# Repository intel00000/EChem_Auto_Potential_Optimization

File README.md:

<!-- @format -->

# Electrochemistry Reactor Controller User Interface

This repository contains a Electrochemistry Reactor Controller User Interface implemented in Python, utilizing multiple microcontrollers for hardware control and a PC-side GUI for experimental automation and operations.

See the [Release Page](https://github.com/intel00000/EChem_Auto_Potential_Optimization/releases) for:

<ol>
  <li>the latest pre-built executable for Windows</li>
  <li>the .uf2 firmwares for microcontroller</li>
  <li>the data post-processing scripts</li>
</ol>

Screenshots of the GUI are shown below. The GUI is designed to be user-friendly, allowing users to easily set up and control the pumps, valves, and other components of the electrochemistry reactor.

## Table of Contents

- [Requirements](#requirements)
- [Setup](#setup)
  - [Native Installation](#native-installation)
  - [Using a Python Virtual Environment (Recommended)](#using-a-python-virtual-environment-recommended)
- [Running the Application](#running-the-application)
- [Compiling to an Executable](#compiling-to-an-executable)
- [Usage](#usage)
- [File Descriptions](#file-descriptions)

## Requirements

- Python 3.11 or higher
- Pip package manager

## Setup (two methods)

### 1. Native Installation

1. Clone the repository:
   ```sh
   git clone https://github.com/intel00000/EChem_Auto_Potential_Optimization.git
   cd EChem_Auto_Potential_Optimization
   ```
2. Install required Python libraries:
   ```sh
   pip install -r requirements.txt -U
   ```
3. Run the Pump Controller Demo with the following command:
   ```sh
   cd pump_control_gui
   python pump_control.py
   ```

### 2. Using a Python Virtual Environment (Recommended)

It is recommended to use a Python virtual environment for better dependency management, especially when compiling the executable. See https://docs.python.org/3/library/venv.html for more details.

#### Windows

1. Open a Windows Powershell and navigate to the project directory.
2. Create a virtual environment:
   ```sh
   python -m venv .venv
   ```
3. Activate the virtual environment:
   ```sh
   .\.venv\Scripts\Activate.ps1
   ```
   If this fail, you might need to run this command first, see https://stackoverflow.com/questions/54776324/powershell-bug-execution-of-scripts-is-disabled-on-this-system
   ```sh
   Set-ExecutionPolicy -ExecutionPolicy RemoteSigned -Scope LocalMachine
   ```
4. Install the required packages:
   ```sh
   cd pump_control_gui
   pip install -r requirements.txt
   ```
5. To run the Pump Controller Demo, ensure the virtual environment is activated and use the following command:
   ```sh
   python pump_control.py
   ```

#### Linux & MacOS (Untested)

1. Open a terminal and navigate to the project directory.
2. Create a virtual environment:

   In bash, run the following commands (assuming using apt)

   ```sh
   sudo apt-get install python3-venv
   python3 -m venv .venv
   ```

3. Activate the virtual environment:
   ```sh
   source ./.venv/bin/activate
   ```
4. Install the required packages:
   ```sh
   cd pump_control_gui
   pip install -r requirements.txt
   ```
5. To run the Pump Controller Demo, activated the virtual environment first and use the following command:
   ```sh
   python3 pump_control.py
   ```

## Compiling to an Executable

To compile the application to a standalone executable using PyInstaller, it is recommended to use a Python virtual environment.

### Windows

1. Create and activate a virtual environment as described above.
2. Install PyInstaller if you haven't already:
   ```sh
   pip install pyinstaller
   cd pump_control_gui
   ```
3. Run PyInstaller to compile the executable:

   ```sh
   pyinstaller pump_control_console.spec
   ```

   OR

   ```sh
   pyinstaller pump_control_noconsole.spec
   ```

4. After the process completes, you will find the executable in the `dist` directory.

## Usage

1. Connect your Raspberry Pi Pico to your PC via a USB cable.
2. Open the executable or run the Python script as described above.
3. Select the appropriate COM port and click "Connect".
4. Load the recipe file by clicking the "Load Recipe" button and selecting your recipe file (CSV or Excel format).
5. Click "Start" to begin the procedure. The GUI will display the progress and status of each pump.

## File Descriptions

- `main.py`: The main entry point for the Raspberry Pi Pico script. It calls the `main` function from `pump_control_pico.py`.
- `pump_control_pico.py`: Contains the logic for controlling the pumps connected to the Raspberry Pi Pico.
- `pwm_dma_fade_onetime.py`: Fade the onboard led of the pi pico using DMA & PWM without using logic core. (Currently don't work for Pi Pico W where the onboard led is controlled by the wifi chip.)

- `pump_control.py`: The Python script for the PC-side GUI, allowing users to interact with the pumps, load recipes, and monitor progress.

### Example Recipe File

An example of a recipe file structure (CSV or Excel):

```csv
Time point (min),Pump 1,Pump 2,Pump 3,Valve 1,Valve 2,Valve 3,Notes
0,On,Off,Off,CW,CW,CW,Start initial fill with reaction solution
0.5,Off,On,On,CCW,CCW,CCW,For testing
1,On,On,Off,,,For testing
5,Off,,,,,,
125,,On,,CW,CW,CW,Post reaction emptying
130,,Off,,,,
130,,On,CCW,CCW,CCW,3x rinse with solvent
135,,Off,,,,
135,,On,CW,CW,CW,
140,,Off,,,,
140,,On,CCW,CCW,CCW,
145,,Off,,,,
145,,On,CW,CW,CW,
150,,Off,,,,
150,,On,CCW,CCW,CCW,
155,,Off,,,,
```

```excel
Time point (min)	Pump 1	Pump 2	Pump 3	Valve 1	Valve 2	Valve 3	Notes
0	                OFF	    OFF	    OFF	    CW	    CW	    CW	    1
0.2	                ON	    ON	    ON	    CCW	    CCW	    CCW	    2
0.4	                OFF	    OFF	    OFF	    CW	    CW	    CW	    3
0.6	                ON	    ON	    ON	    CCW	    CCW	    CCW	    4
0.8	                OFF	    OFF	    OFF	    CW	    CW	    CW	    5
1	                ON	    ON	    ON	    CCW	    CCW	    CCW	    6
1.2	                OFF	    OFF	    OFF	    CW	    CW	    CW	    7
1.4	                ON	    ON	    ON	    CCW	    CCW	    CCW	    8
1.6	                OFF	    OFF	    OFF	    CW	    CW	    CW	    9
1.8	                ON	    ON	    ON	    CCW	    CCW	    CCW	    10
```

Ensure the `Time point (min)` column is sorted in ascending order.

## PCB Design

Inside the control_board_Kicad folder is a KiCad project for the control board design. The control board is designed to plug into a pump with a DB25 connector which allow one pico to control one pump respectively.
Using a PCB enable secure and reliable connection between the pump and the pico, and also allow for easy expansion of the system.

## Contact

For any issues or contributions, please open an issue or pull request on GitHub.

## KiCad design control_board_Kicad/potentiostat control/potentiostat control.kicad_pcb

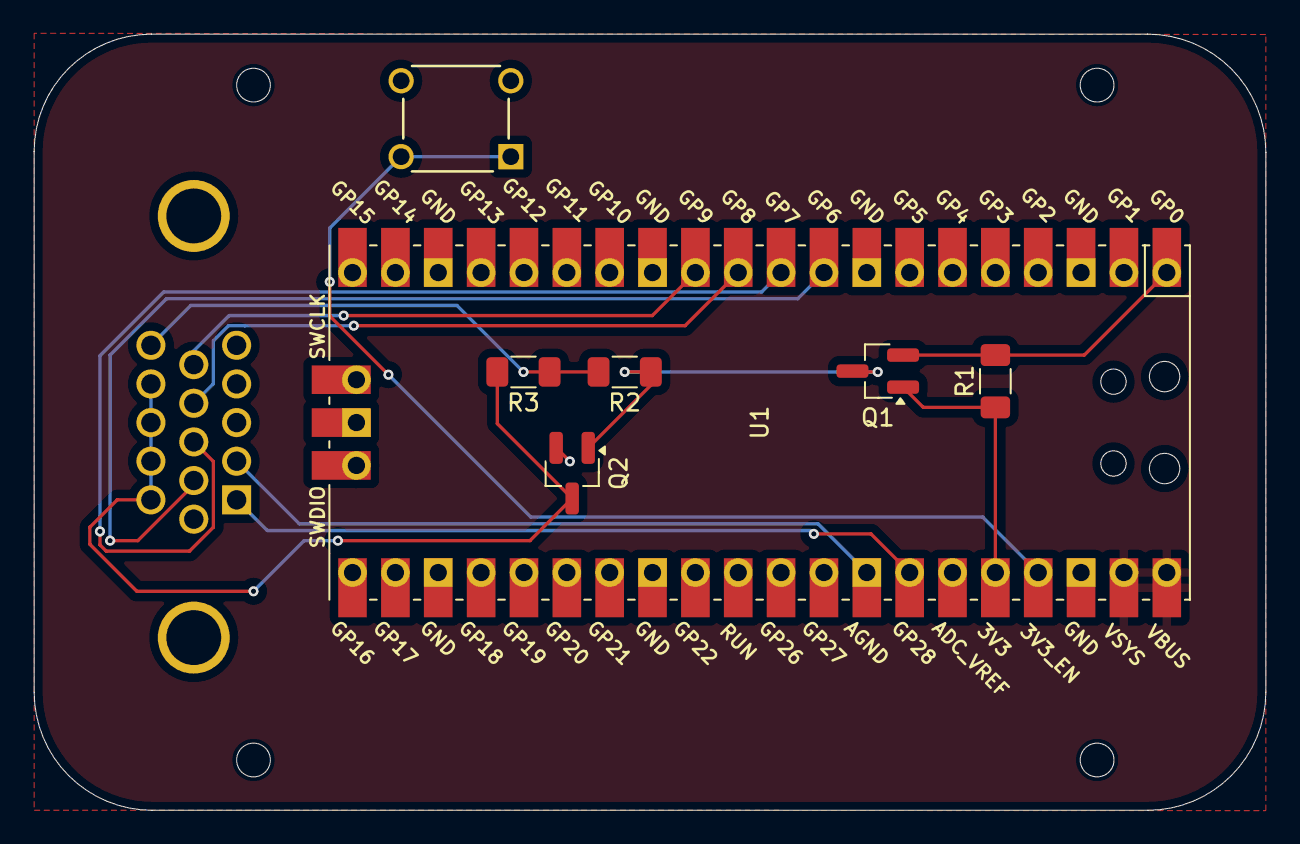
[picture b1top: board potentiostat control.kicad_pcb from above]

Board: 2 copper layers, 73.0 x 46.0 mm, 8 parts (1 on the bottom side), 14 nets.

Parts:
J1: L717HDE15PD1CH4F; AMPHENOL_L717HDE15PD1CH4F
Q1, Q2: 2N7002; SOT-23_Handsoldering
R1, R2, R3: 4.7 kΩ; R_1206_3216Metric_Pad1.30x1.75mm_HandSolder
SW1: 3-1825910-5; SW4_1825910-I_TEC
U1: Raspberry Pi Pico; RPi_Pico_SMD_TH

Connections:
+3.3V: Q1.1 (G), R1.1, U1.36 (3V3_OUT)
+5V: U1.39 (VSYS), U1.40 (VBUS)
+5VP: J1.15, R2.2, R3.1
AGND: J1.2, U1.33 (AGND)
GND: J1.6, Q2.2 (S), SW1.3, SW1.4, U1.3 (GND), U1.8 (GND), U1.13 (GND), U1.18 (GND), U1.23 (GND), U1.28 (GND), U1.38 (GND)
unnamed: Q1.3 (D), Q2.1 (G), R2.1
unnamed: Q1.2 (S), R1.2, U1.1 (GP0)
unnamed: J1.11, J1.12, J1.13, J1.14, Q2.3 (D), R3.2
unnamed: SW1.1, SW1.2, U1.37 (3V3_EN)
unnamed: J1.7, U1.9 (GP6)
unnamed: J1.8, U1.10 (GP7)
unnamed: J1.9, U1.11 (GP8)
unnamed: J1.10, U1.12 (GP9)
unnamed: J1.1, U1.34 (GP28)

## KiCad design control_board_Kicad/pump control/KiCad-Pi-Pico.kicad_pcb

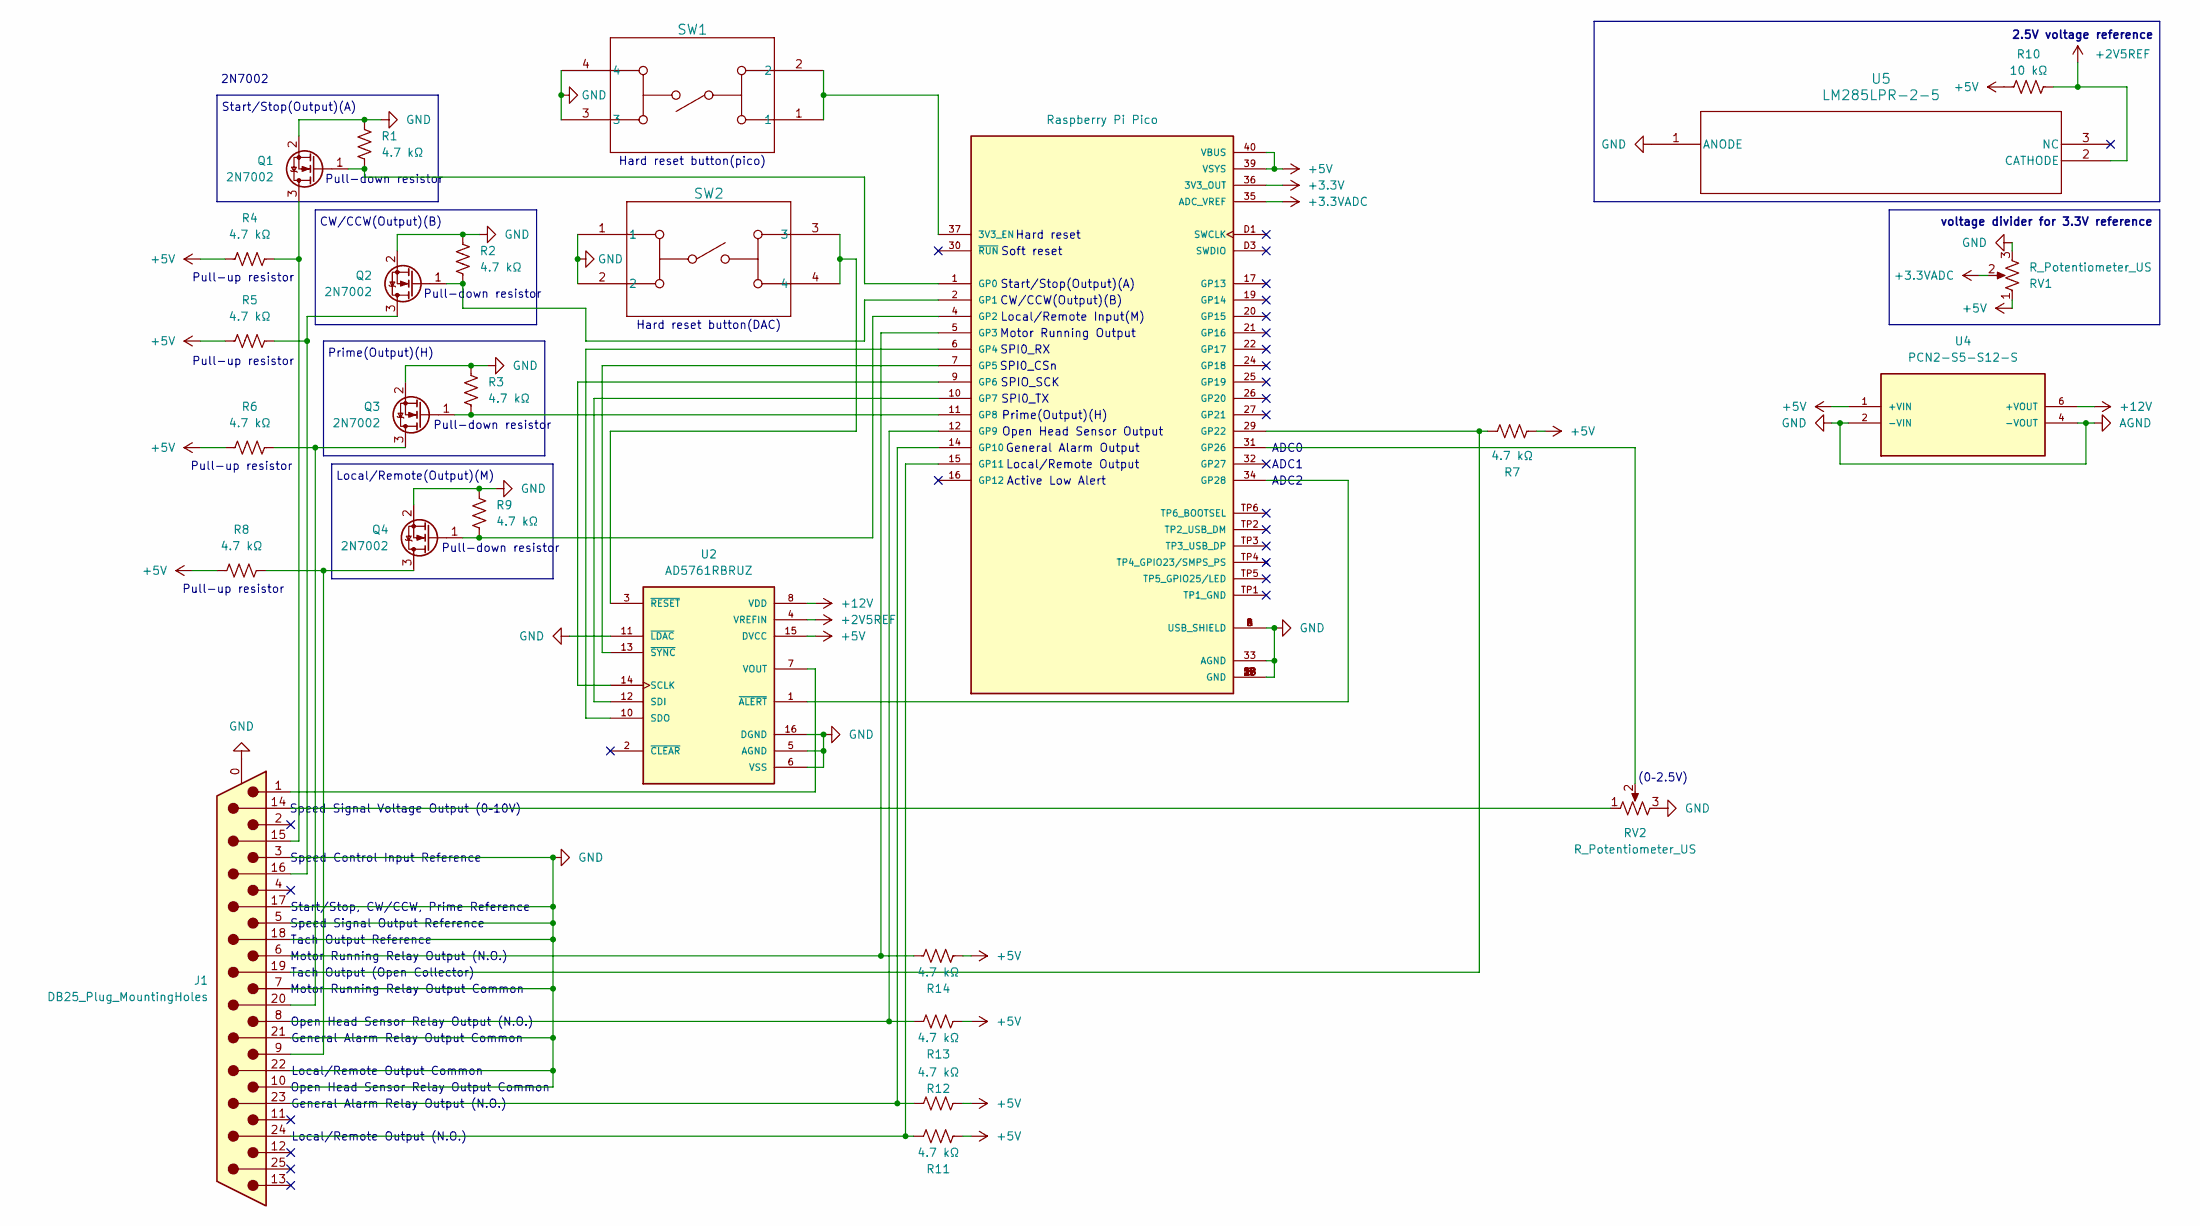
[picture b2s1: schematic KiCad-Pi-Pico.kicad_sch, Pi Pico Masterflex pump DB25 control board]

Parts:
J1: DB25_Plug_MountingHoles; DSUB-25_Male_Horizontal_P2.77x2.84mm_EdgePinOffset4.94mm_Ho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
Q1, Q2, Q3, Q4: 2N7002; SOT-23
R1, R2, R3, R4, R5, R6, R7, R8, R9, R11, R12, R13, R14: 4.7 kΩ; R_1206_3216Metric_Pad1.30x1.75mm_HandSolder
R10: 10 kΩ; R_1206_3216Metric_Pad1.30x1.75mm_HandSolder
RV1, RV2: R_Potentiometer_US; Potentiometer_Bourns_3386W_Horizontal
SW1, SW2: 3-1825910-5; SW4_1825910-I_TEC
U1: Raspberry Pi Pico; MODULE_SC0915; PARTREV 1.6
U2: AD5761RBRUZ; SOP65P640X120-16N; DigiKey_Part_Number 505-AD5761RBRUZ-ND
U4: PCN2-S5-S12-S; CONV_PCN2-S5-S12-S; PARTREV 1.0
U5: LM285LPR-2-5; LP3

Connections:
+2V5REF: R10.2, U2.4 (VREFIN), U5.2 (CATHODE)
+3.3V: U1.36 (3V3_OUT)
+3.3VADC: RV1.2, U1.35 (ADC_VREF)
+5V: R4.1, R5.1, R6.1, R7.1, R8.1, R10.1, R11.1, R12.1, R13.1, R14.1, RV1.1, U1.39 (VSYS), U1.40 (VBUS), U2.15 (DVCC), U4.1 (+VIN)
+12V: U2.8 (VDD), U4.6 (+VOUT)
GND: J1.0 (PAD), J1.3, J1.5, J1.7, J1.10, J1.17, J1.18, J1.21, J1.22, Q1.2 (S), Q2.2 (S), Q3.2 (S), Q4.2 (S), R1.2, R2.2, R3.2, R9.2, RV1.3, RV2.3, SW1.3, SW1.4, SW2.1, SW2.2, U1.3 (GND), U1.8 (GND), U1.13 (GND), U1.18 (GND), U1.23 (GND), U1.28 (GND), U1.33 (AGND), U1.38 (GND), U1.A (USB_SHIELD), U1.B (USB_SHIELD), U1.C (USB_SHIELD), U1.D (USB_SHIELD), U1.D2 (GND), U2.5 (AGND), U2.6 (VSS), U2.11 (~LDAC), U2.16 (DGND), U4.2 (-VIN), U4.4 (-VOUT), U5.1 (ANODE)
unnamed: J1.14, RV2.1
unnamed: J1.15, Q1.3 (D), R4.2
unnamed: J1.16, Q2.3 (D), R5.2
unnamed: J1.19, R7.2, U1.29 (GP22)
unnamed: J1.20, Q3.3 (D), R6.2
unnamed: J1.23, R12.2, U1.14 (GP10)
unnamed: J1.24, R11.2, U1.15 (GP11)
unnamed: Q1.1 (G), R1.1, U1.1 (GP0)
unnamed: Q2.1 (G), R2.1, U1.2 (GP1)
unnamed: Q3.1 (G), R3.1, U1.11 (GP8)
unnamed: J1.9, Q4.3 (D), R8.2
unnamed: Q4.1 (G), R9.1, U1.4 (GP2)
unnamed: SW1.1, SW1.2, U1.37 (3V3_EN)
unnamed: J1.6, R14.2, U1.5 (GP3)
unnamed: U1.6 (GP4), U2.10 (SDO)
unnamed: U1.7 (GP5), U2.13 (~SYNC)
unnamed: U1.9 (GP6), U2.14 (SCLK)
unnamed: U1.10 (GP7), U2.12 (SDI)
unnamed: J1.8, R13.2, U1.12 (GP9)
unnamed: RV2.2, U1.31 (GP26)
unnamed: U1.34 (GP28), U2.1 (~ALERT)
unnamed: J1.1, U2.7 (VOUT)
unnamed: SW2.3, SW2.4, U2.3 (~RESET)

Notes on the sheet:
2.5V voltage reference
Pull-down resistor
Prime(Output)(H)
Motor Running Relay Output Common
Pull-up resistor
Hard reset button(DAC)
ADC2
SPI0_RX
Hard reset button(pico)
Open Head Sensor Relay Output Common
SPI0_CSn
Hard reset
Tach Output Reference
Local/Remote Output (N.O.)
Open Head Sensor Relay Output (N.O.)
2N7002
Open Head Sensor Output
General Alarm Output
Local/Remote Output Common
Speed Signal Output Reference
SPIO_SCK
Local/Remote Output
Speed Control Input Reference
General Alarm Relay Output Common
(0–2.5V)
Start/Stop(Output)(A)
voltage divider for 3.3V reference
Soft reset
Local/Remote Input(M)
Speed Signal Voltage Output (0–10V)
Active Low Alert
SPI0_TX
Motor Running Output
General Alarm Relay Output (N.O.)
CW/CCW(Output)(B)
Local/Remote(Output)(M)
ADC0
Motor Running Relay Output (N.O.)
ADC1
Start/Stop, CW/CCW, Prime Reference

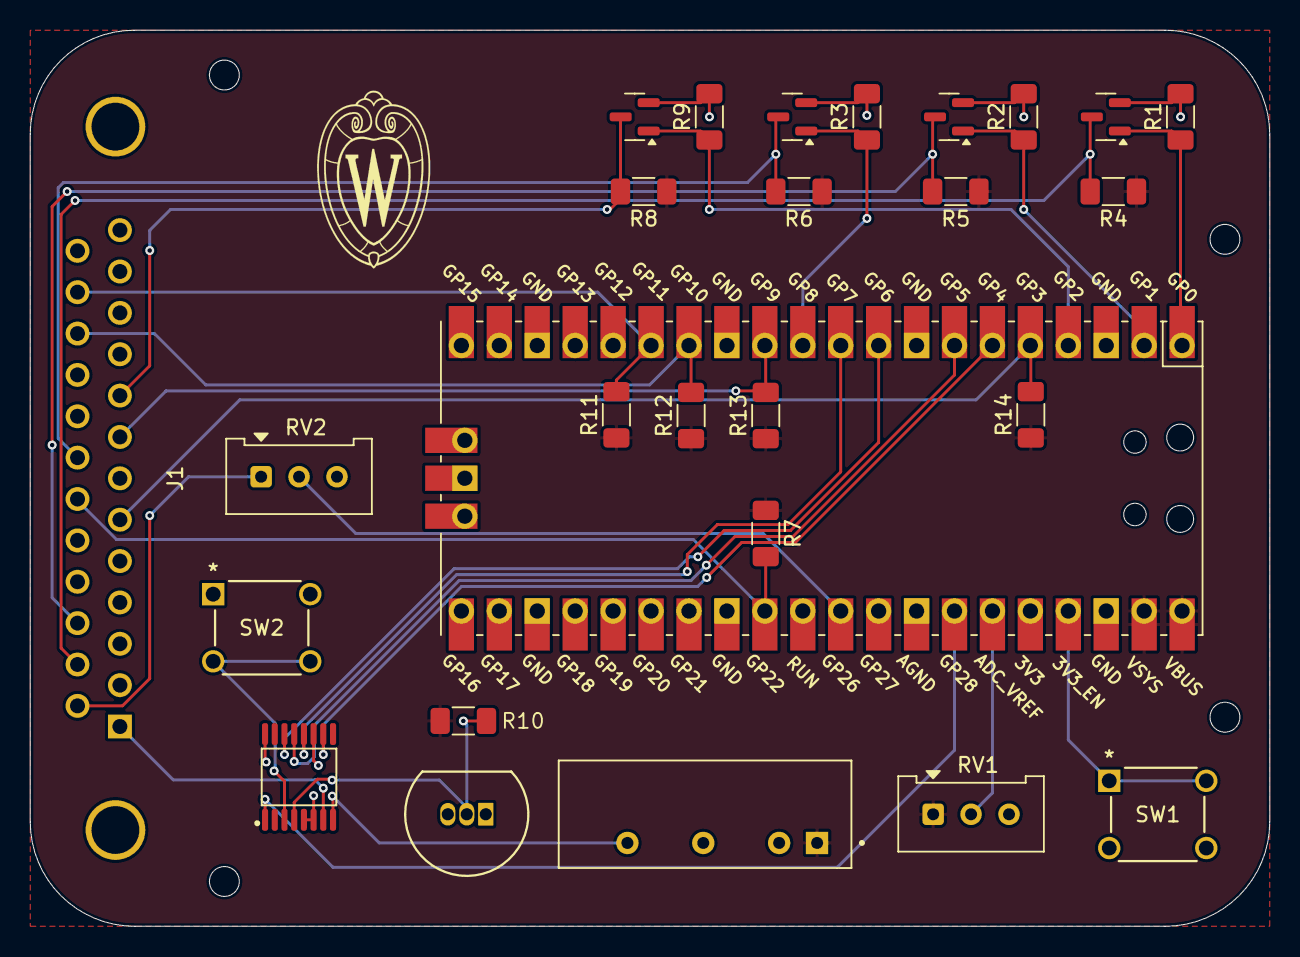
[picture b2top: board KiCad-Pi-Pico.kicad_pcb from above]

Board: 2 copper layers, 83.0 x 60.0 mm, 27 parts (1 on the bottom side), 28 nets.

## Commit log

2024-05-31 init repo
2024-05-31 some ideas
2024-06-04 DOE update script
2024-06-07 search function for jaggaer website complete
2024-06-07 some refinement to the search function
2024-06-13 6/13 update using LogixDriver at this point
2024-06-13 updated gitignore
2024-06-13 test_script for CIPDriver connection
2024-06-15 simple testing on pi pico
2024-06-17 testing with pi pico multithread & ADC
2024-06-17 Time stamp & ADC pulling by PC
2024-06-26 pump pico controller
2024-07-06 explore the pi pico ADC limit
2024-07-07 mark
2024-07-08 GIL causing problem
2024-07-08 single thread solve the issues
2024-07-08 working demo
2024-07-08 update gitignore
2024-07-08 add README.md
2024-07-08 add openpyxl
2024-07-10 update for Mac
2024-07-12 separate into frontend and backend
2024-07-13 update pico script to allow dynamic pump addition and change
2024-07-14 adding pause function
2024-07-14 filename change
2024-07-14 port to pyqt6
2024-07-16 fade onboard led using chain dma channel
2024-07-16 compile the gui
2024-07-17 qt port update
2024-07-21 blink when receive command
2024-07-23 prototype testing
2024-07-23 add AD5761
2024-07-23 add manual
2024-07-26 folder name change
2024-07-27 tkinter already included with python
2024-07-27 add exe
2024-07-27 add Kicad design file
2024-07-27 change padding
2024-07-27 add Mac executable
2024-07-27 add style sheet
2024-07-30 update KiCad design
2024-07-30 KiCad update
2024-07-31 add emergency shutdown
2024-07-31 add pump config file
2024-08-01 update exe
2024-08-03 KiCad updated
2024-08-05 remove exe
2024-08-14 frequency measurement testing
2024-08-14 PCB design finished
2024-08-15 add MacOS executable
2024-08-15 update the reciprocal method
2024-08-15 add interrupt to sync the signal
2024-08-30 update README for linux
2024-09-05 experiment with DOE workflow
2024-09-10 early testing of DOE plot and regression
2024-09-11 UI change for the autosampler
2024-09-11 testing with autosampler
2024-09-12 encapsulate autosampler method in class
2024-09-12 add scheduler function
2024-09-12 switch to non-blocking message block
2024-09-12 compile exe
2024-09-13 sync with setup
2024-09-14 add system tray
2024-09-16 edit README.md
2024-09-16 file change
2024-09-25 update PCB design
2024-09-29 PCD 1st version
2024-09-30 AD5761 implementation
2024-10-01 update ad5761 document
2024-10-01 refractor pulse measurement into class
2024-10-01 change to spec file
2024-10-01 change file structure
2024-10-01 update spec
2024-10-15 update DOE
2024-10-15 host page on github
2024-10-16 update echem animated plot
2024-10-16 testing workflow
2024-10-16 testing again
2024-10-16 Auto-generate index.html from GitHub Actions
2024-10-16 update pages styles
2024-10-16 update pages
2024-11-17 adapting to multiple controller
2024-11-18 refactor code
2024-11-18 update icons paths
2025-01-17 update KiCad
2025-01-23 add autosampler design
2025-01-23 gamry framework parsing
2025-01-23 Add Gsequence generator
2025-01-24 update board
2025-01-27 update main program
2025-01-28 update layout
2025-01-31 update LOCK_FILE
2025-01-31 update result graphing script
2025-01-31 update index page
2025-01-31 retrack html
2025-01-31 update workflow
2025-01-31 Update generate-index.yml
    install pytz
2025-01-31 testing the workflow
2025-02-17 combined sequence generation
2025-02-17 update pyinstaller spec
2025-02-17 fix Excel file reading
2025-02-19 fix GSequence generation
2025-02-20 add save directory settings
2025-02-20 fix the combo box update
2025-02-26 enable dpi awareness under windows
2025-02-26 fix layout resizing
2025-02-26 fix scaling factor
2025-02-26 add a bootloader to the firmware
2025-02-26 complete bootloader testing
2025-03-04 add firmware update page
2025-03-16 add new experiment data
2025-03-16 refactor autosampler script into arduino
2025-03-16 fix a error in the graph generation notebook
2025-03-17 add a basic ramp up/ramp down
2025-03-17 added slot config
2025-03-20 finishing up the new autosampler control
2025-03-20 minor fix
2025-03-22 add pio method to gate pwm signal
2025-03-31 fix empty command issues
2025-04-02 clean up folder
2025-04-02 updating gui
2025-04-02 add new result
2025-04-11 added potentiostat control mpython
2025-04-14 retrack files
2025-04-14 update gui
2025-04-16 update firmware update page
2025-04-16 finish potentiostat implementation
2025-04-16 update time display
2025-04-18 fixing minor issues
2025-04-23 using customtkinter
2025-04-23 switching back to labelframe
2025-05-05 renamed DOE script
2025-05-05 retrack ipynb
2025-05-05 update DOE template notebook
2025-05-08 update tkinter
2025-05-09 testing arduino fw flashing
2025-05-10 restructure pages
2025-05-12 restructure folder
2025-05-12 Create build-micropython.yml
    add mpy build workflow
2025-05-12 testing new workflow
2025-05-12 Update build-micropython.yml
    fix make modules
2025-05-12 testing workflow again
2025-05-12 Auto-build MicroPython firmware from mpy_fw_included changes
2025-05-14 update plotting
2025-05-26 finish adding all blink led function
2025-05-27 update pyinstall spec file
2025-05-28 update pyinstaller spec files
2025-05-28 add graphs
